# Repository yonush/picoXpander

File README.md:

# Tangible Learning for IoT and Automation ... in a Lunchbox - the picoXpander

This repo is the design files and sample code for the picoXpander kit. It is kit that leverages the Raspberry pico boards (RP2040 & RP2350) as a controller along with various IO boards the connect up using a short ribbon cable. The goal of this kit was to use simple technology to make an interesting electronics kit for teaching at a very affordable price. The focus of the learning is on the programming and understanding logic. This reduces the reliance on the connection and wiring up of individual components which take more time to get right. 

The Lunch box idea idea was create boards that are small enough to fit into a 1L box (about 160L x 113W x 90H mm in size. Like this one from [Living & Co.](https://www.thewarehouse.co.nz/p/living-co-storage-container-rectangle-assorted-1l/R2039528.html)), including the cable. This meant it was easy to keep the kit together and carry around. The 1L box has enough room to fit about 6-7 boards and the USB cable. An example of the lunch with three boards, cable and infomation card can be seen below.

## Software

The kit IO layout was arranged to match the [picoPLC](https://github.com/yonush/PicoPLC) pinout so that you can write your applications using [OpenPLC](https://autonomylogic.com/), CircuitPython, Micropython or C/C++, Python (with Blinka), TinyGo, Nim and Assemnby if you wish. Basically anything that can run on the Raspberyr Pico would work.

Pinout used by the picoXpander and picoPLC

### Using Blinka from Adafruit

Support has been added to work with the Adafruit Blinka platform with some caveats. IN order to match the above pinout and work with the piocPLC there were several changes made to the Adafruit Blinka module. With a summary of the changes below. A more detailed writeup can be found in the [readme](blinka/READ.me) for the picoXpander blinka distribution.

**Changes made to adafruit_blinka module**

The picoXpander driver board uses an off the shelf Raspberry Pico device which means there were no changes made to the USB HID (device VID) settings. We modified the existing rp2040_u2if driver, changes can be found in the blinka folder.

## The boards in brief

There are seven boards identified for the kit with three of them already designed and tested with the other four in progress

- :white_check_mark: Raspberry Pico driver board
- :white_check_mark: Traffic light crossing
- :white_check_mark: 8bit digital I/O
- :white_large_square: Four floor elevator
- :white_large_square: 16x8 LED display
- :white_check_mark: Breakout & passthrough board
- :white_large_square: Multiple sensor board
- :white_large_square: Motor/Servo driver board

### The picoXpander driver board

This board contains a socket for the Pico which also provision for direct soldering of the pico to the board. There is a room for a small I2C OLED display. (supports 0.91", 0.96", 1.3", 1.5" and 2.43" displays). 

- It is 106x88mm in size
- There are 26 buffered LEDs, one for each of the GPIO pins  than connect to the . 
- No external power required.
- Has a convenient reset button
- The I2C can be remapped to "network" two boards using the UART.

### Traffic crossing

This simulates 4 way crossing with a pedestrian light for two of the roads. 

- It is 130x88mm in size
- Three buttons to interact with the lights
- 16 LEDs arrange as 3 per intersection. opposite traffic lights are tied together
- No external power required.

### 8bit Digital IO board

A simple board the maps against the 8 digital inputs and 8 digital outputs. The labels of the buttons are not tied to a specific function but can be used as identifiers.

### Four floor elevator

A board to simulate a elevator with four floors.

- 1 button for each floor to call the elevator 
- 2 LEDs to indicate elevator traveling up or down
- 4 buttons for the inside of the elevator
- 4 LEDs in a box to represent the elevator at each floor
- 1 Analog input for the floor feedback (resistor network)

*Design currently under development.*

### 16x9 LED display

Contains a 16x9 Charlieplexed LED matrix to present a very simple display driven by the rather convenient IS31FL3731 LED display chip.

- 16x9 LEDs (colour yet to be determined)
- 1x 4 way button joystick
- 2x additional buttons for interaction
- 1x Haptic feedback motor

*Design currently under development.*

### Breakout & passthrough board

This board can either be attach to the driver board or between the driver board and another board. It provides the IO passthrough but also a header to allow you to attach dupont leads. A small breadboard is also attached to let you add components not found on the fixed function boards. A 6pin header has been added to provide connectivity for two small servos such as the [MG90S](https://components101.com/motors/mg90s-metal-gear-servo-motor) and the [SG90](https://components101.com/motors/servo-motor-basics-pinout-datasheet).

### Multiple sensor board

This board contains several common sensors and a a couple of RGB LEDs. Starting with the smart sensor BME688. It is an air quality sensor can measure gas, temperature, pressure and humiditthe first gas sensor with Artificial Intelligence  

Sensor list

- Light sensor
- Sound
- Air quality
- Temperature
- Humidity
- Motion
- Pressure

*Design currently under development.*

### Motor/Servo driver board

This board will have a motor driver for two motors to let you attach the pixoXpander to a chassi

- 1x H-bridge motor driver, with built-in short circuit, over current and thermal protection.
- [alt] DRV8833 motor driver using I2C - 1A per motor
- [alt] MX1508 motor driver using PWM - 1.5A per motor
- 2x motors or 1x stepper
- Uses external power with on board charger for a battery
- 4x servo outputs
- power switch for the external power

*Design currently under development.*

## Demo code

*Under development*

-end-of-file-

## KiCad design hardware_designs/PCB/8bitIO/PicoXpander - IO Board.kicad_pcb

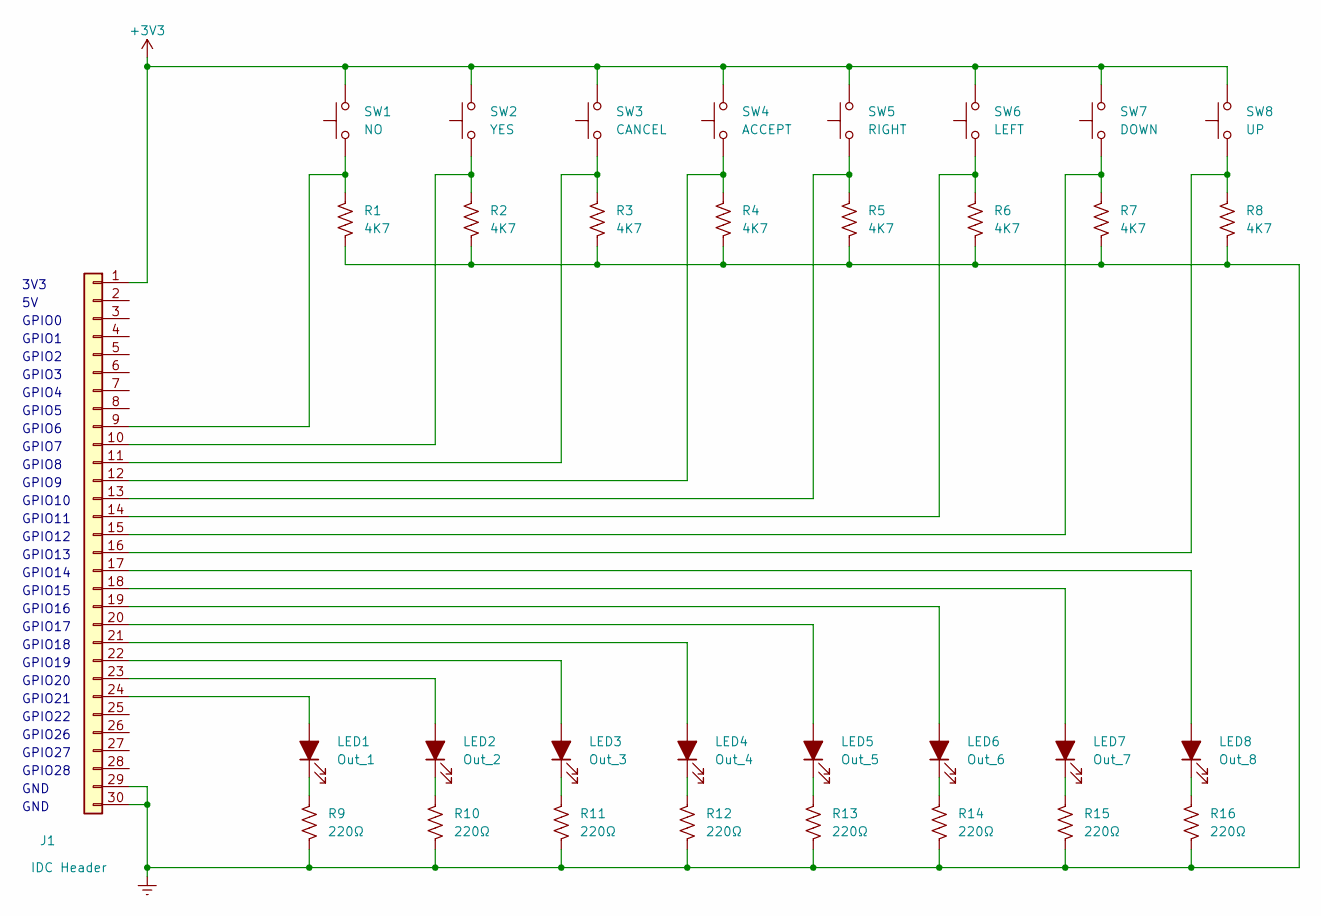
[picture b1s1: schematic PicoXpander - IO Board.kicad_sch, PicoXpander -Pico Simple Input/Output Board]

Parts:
J1: IDC Header; IDC-Header_2x15_P2.54mm_Horizontal
LED1, LED2, LED3, LED4, LED5, LED6, LED7, LED8: Red; LED_0805_2012Metric
R1, R2, R3, R4, R5, R6, R7, R8: 4K7; R_0805_2012Metric
R9, R10, R11, R12, R13, R14, R15, R16: 220Ω; R_0805_2012Metric
SW1: NO; SW_Push_1P1T_NO_6x6mm_H9.5mm
SW2: YES; SW_Push_1P1T_NO_6x6mm_H9.5mm
SW3: CANCEL; SW_Push_1P1T_NO_6x6mm_H9.5mm
SW4: ACCEPT; SW_Push_1P1T_NO_6x6mm_H9.5mm
SW5: RIGHT; SW_Push_1P1T_NO_6x6mm_H9.5mm
SW6: LEFT; SW_Push_1P1T_NO_6x6mm_H9.5mm
SW7: DOWN; SW_Push_1P1T_NO_6x6mm_H9.5mm
SW8: UP; SW_Push_1P1T_NO_6x6mm_H9.5mm

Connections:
+3V3: J1.1, SW1.2, SW2.2, SW3.2, SW4.2, SW5.2, SW6.2, SW7.2, SW8.2
GNDREF: J1.29, J1.30, R1.1, R2.1, R3.1, R4.1, R5.1, R6.1, R7.1, R8.1, R9.1, R10.1, R11.1, R12.1, R13.1, R14.1, R15.1, R16.1
unnamed: J1.9, R1.2, SW1.1
unnamed: J1.10, R2.2, SW2.1
unnamed: J1.11, R3.2, SW3.1
unnamed: J1.12, R4.2, SW4.1
unnamed: J1.13, R5.2, SW5.1
unnamed: J1.14, R6.2, SW6.1
unnamed: J1.15, R7.2, SW7.1
unnamed: J1.16, R8.2, SW8.1
unnamed: J1.17, LED8.2 (A)
unnamed: J1.18, LED7.2 (A)
unnamed: J1.19, LED6.2 (A)
unnamed: J1.20, LED5.2 (A)
unnamed: J1.21, LED4.2 (A)
unnamed: J1.22, LED3.2 (A)
unnamed: J1.23, LED2.2 (A)
unnamed: J1.24, LED1.2 (A)
unnamed: LED1.1 (K), R9.2
unnamed: LED2.1 (K), R10.2
unnamed: LED3.1 (K), R11.2
unnamed: LED4.1 (K), R12.2
unnamed: LED5.1 (K), R13.2
unnamed: LED6.1 (K), R14.2
unnamed: LED7.1 (K), R15.2
unnamed: LED8.1 (K), R16.2

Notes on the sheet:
GPIO13
GPIO19
GPIO0
GPIO3
GPIO17
GPIO20
GPIO21
GPIO2
3V3
GPIO15
GPIO14
GPIO8
GPIO12
GPIO16
GPIO6
GPIO7
GPIO27
GND
GPIO18
GPIO10
GPIO22
GPIO9
GPIO11
GPIO1
GPIO4
GPIO28
GPIO26
GPIO5

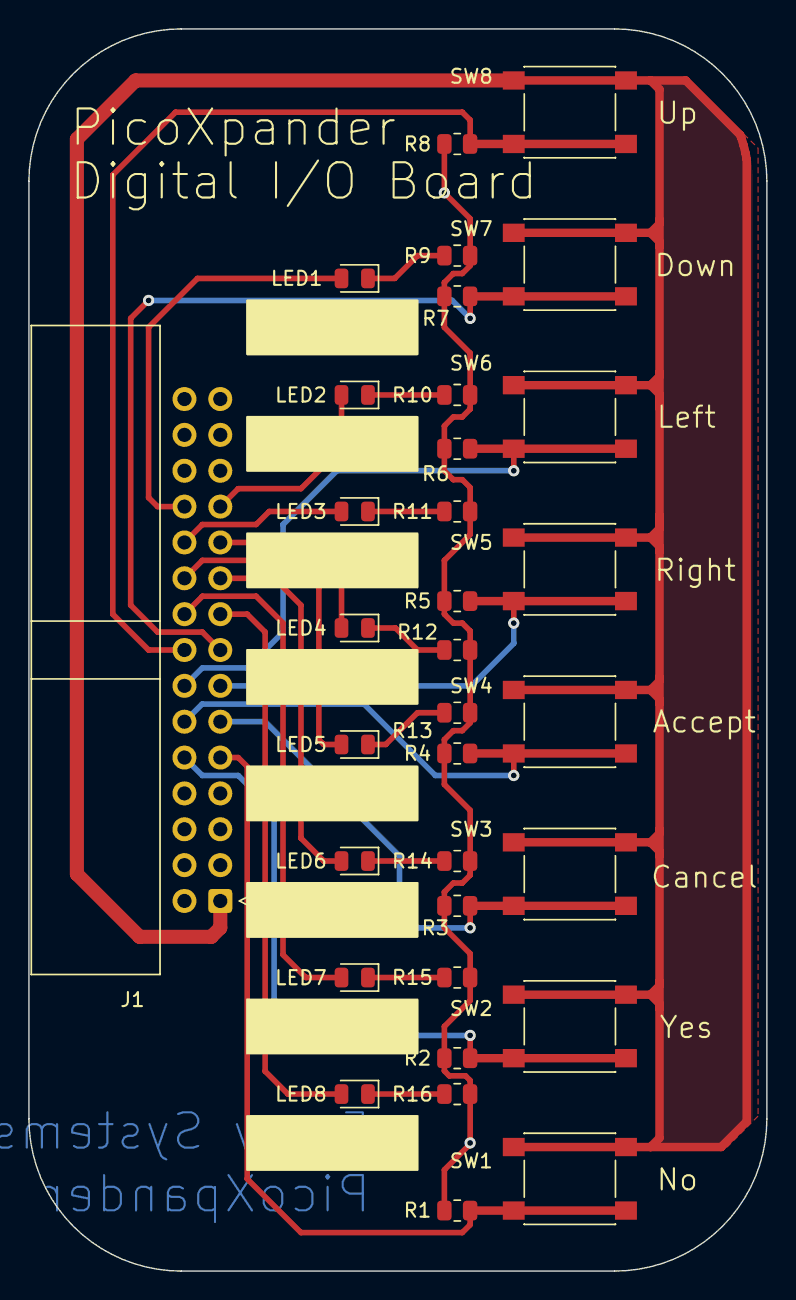
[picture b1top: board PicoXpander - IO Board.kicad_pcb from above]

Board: 2 copper layers, 52.3 x 88.0 mm, 33 parts (0 on the bottom side), 26 nets.

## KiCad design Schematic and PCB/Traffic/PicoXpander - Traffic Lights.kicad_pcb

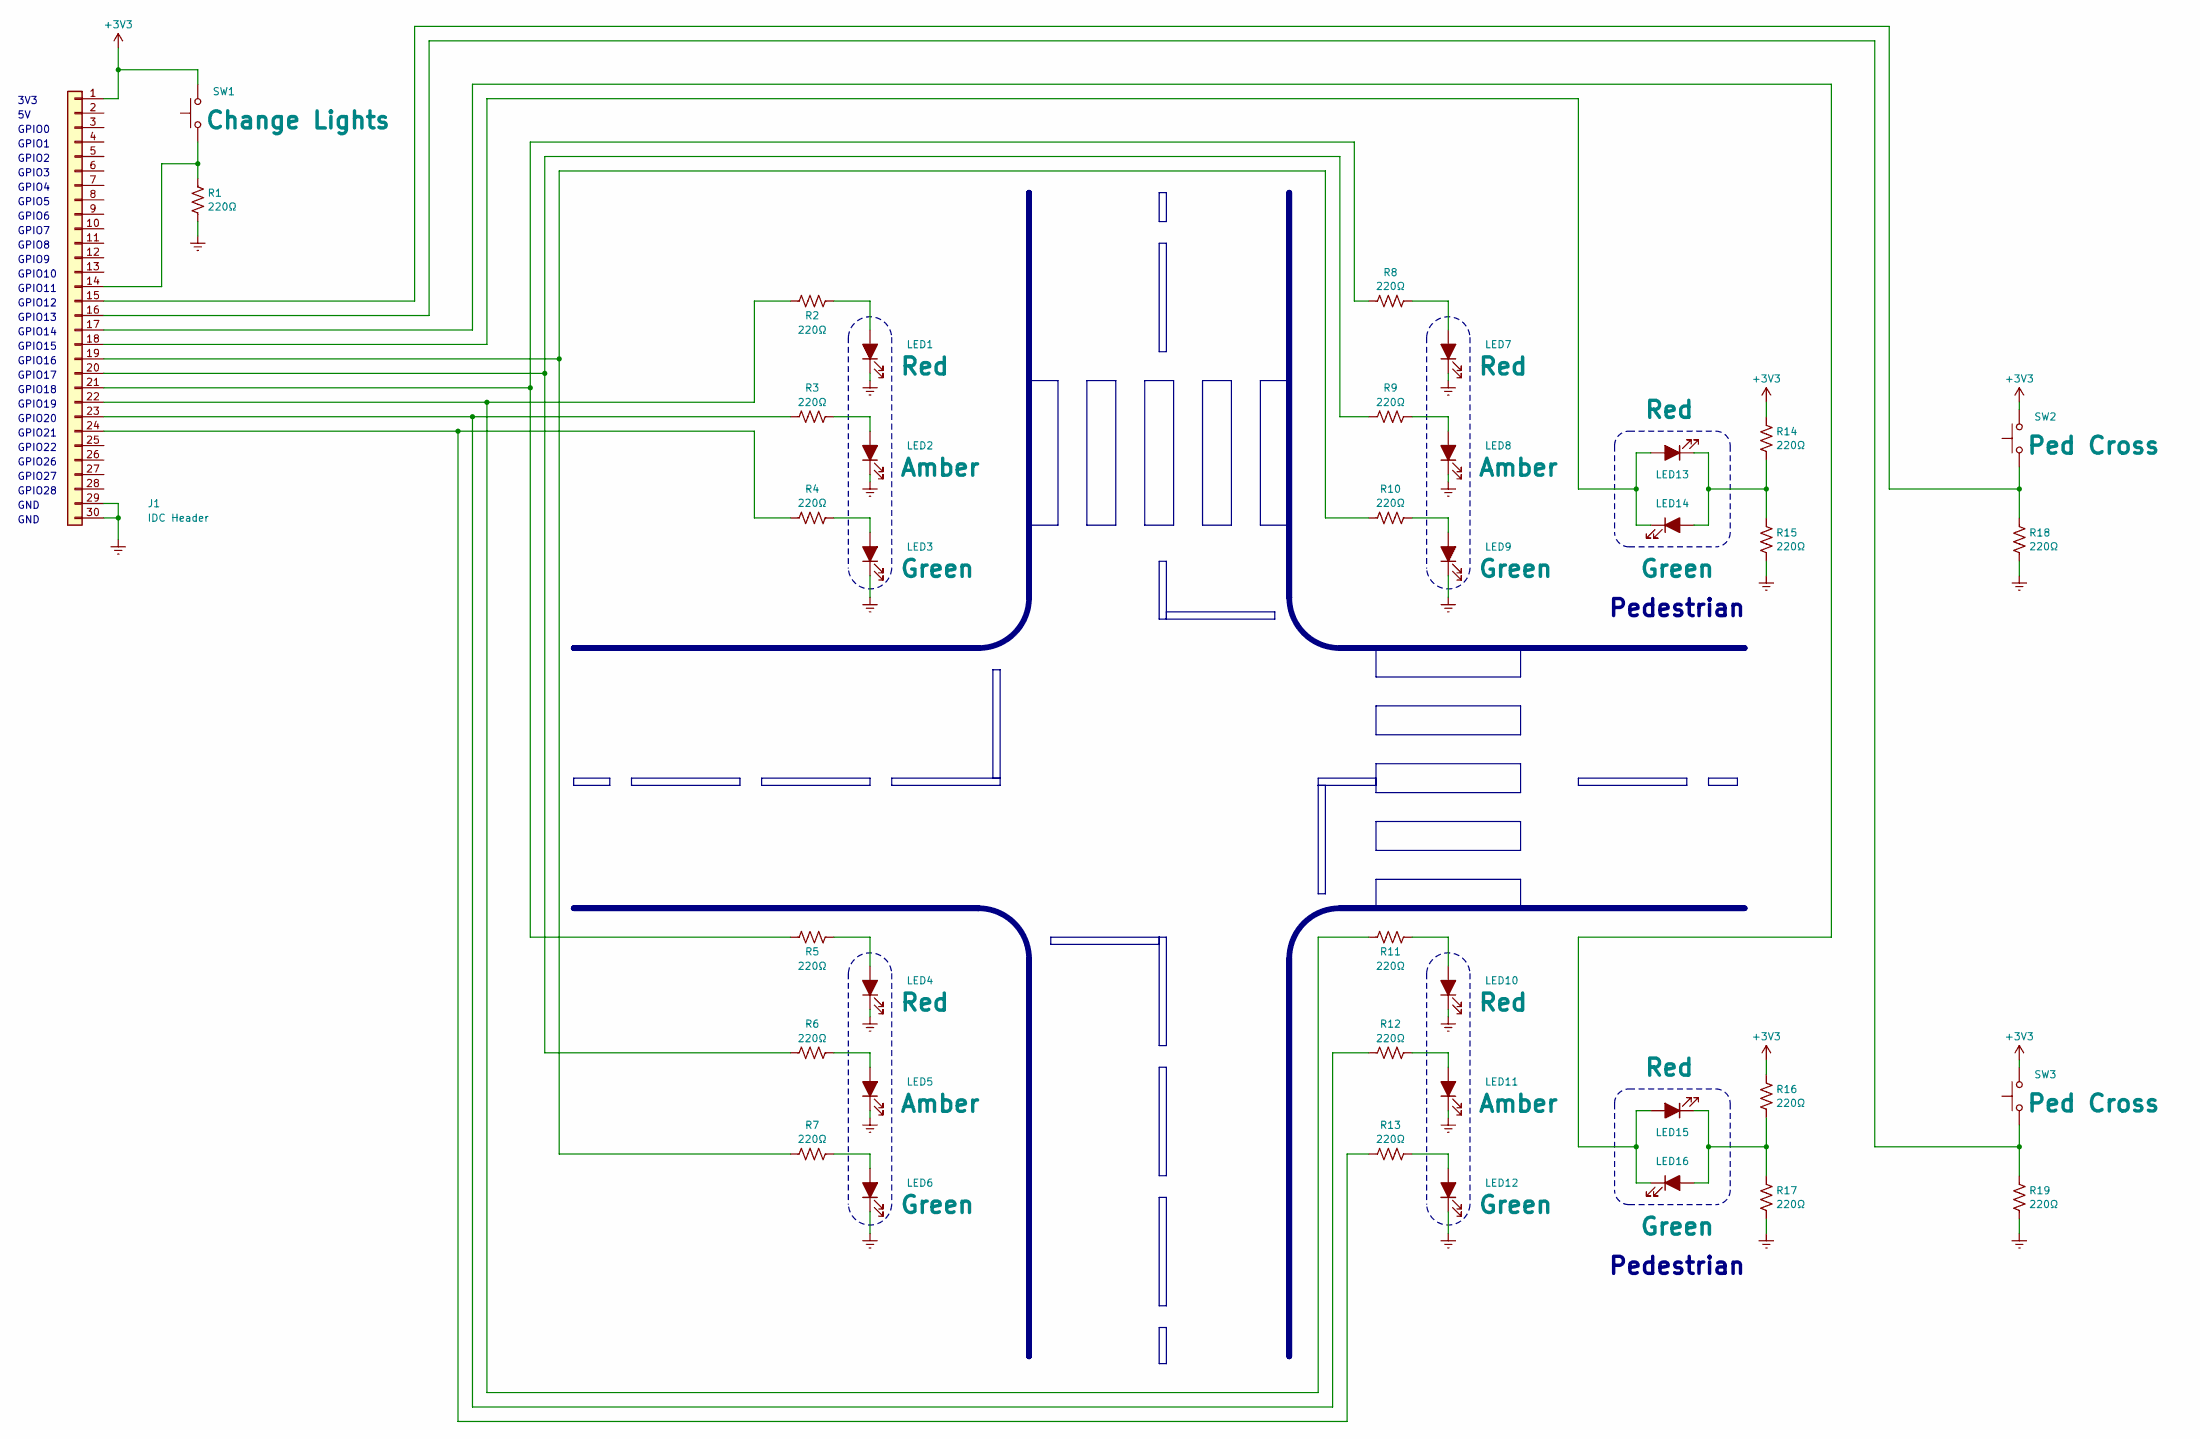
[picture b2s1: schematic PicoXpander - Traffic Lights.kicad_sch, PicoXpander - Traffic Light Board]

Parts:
J1: IDC Header; IDC-Header_2x15_P2.54mm_Horizontal
LED1, LED4, LED7, LED10, LED13, LED15: Red; LED_0805_2012Metric
LED2, LED5, LED8, LED11: Amber; LED_0805_2012Metric
LED3, LED6, LED9, LED12, LED14, LED16: Green; LED_0805_2012Metric
R1, R2, R3, R4, R5, R6, R7, R8, R9, R10, R11, R12, R13, R14, R15, R16, R17, R18, R19: 220Ω; R_0805_2012Metric
SW1: Change Lights; SW_Push_1P1T_NO_6x6mm_H9.5mm
SW2, SW3: Ped Cross; SW_Push_1P1T_NO_6x6mm_H9.5mm

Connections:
+3V3: J1.1, R14.2, R16.2, SW1.2, SW2.2, SW3.2
GNDREF: J1.29, J1.30, LED1.1 (K), LED2.1 (K), LED3.1 (K), LED4.1 (K), LED5.1 (K), LED6.1 (K), LED7.1 (K), LED8.1 (K), LED9.1 (K), LED10.1 (K), LED11.1 (K), LED12.1 (K), R1.1, R15.1, R17.1, R18.1, R19.1
unnamed: J1.14, R1.2, SW1.1
unnamed: J1.15, R18.2, SW2.1
unnamed: J1.16, R19.2, SW3.1
unnamed: J1.17, LED15.2 (A), LED16.1 (K)
unnamed: J1.18, LED13.2 (A), LED14.1 (K)
unnamed: J1.19, R7.1, R10.1
unnamed: J1.20, R6.1, R9.1
unnamed: J1.21, R5.1, R8.1
unnamed: J1.22, R2.1, R11.1
unnamed: J1.23, R3.1, R12.1
unnamed: J1.24, R4.1, R13.1
unnamed: LED1.2 (A), R2.2
unnamed: LED2.2 (A), R3.2
unnamed: LED3.2 (A), R4.2
unnamed: LED4.2 (A), R5.2
unnamed: LED5.2 (A), R6.2
unnamed: LED6.2 (A), R7.2
unnamed: LED7.2 (A), R8.2
unnamed: LED8.2 (A), R9.2
unnamed: LED9.2 (A), R10.2
unnamed: LED10.2 (A), R11.2
unnamed: LED11.2 (A), R12.2
unnamed: LED12.2 (A), R13.2
unnamed: LED13.1 (K), LED14.2 (A), R14.1, R15.2
unnamed: LED15.1 (K), LED16.2 (A), R16.1, R17.2

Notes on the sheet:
GPIO13
GPIO19
GPIO0
GPIO3
GPIO17
GPIO20
GPIO21
GPIO2
3V3
GPIO15
GPIO14
Pedestrian
GPIO8
GPIO12
GPIO16
GPIO6
GPIO7
GPIO27
GND
GPIO18
GPIO10
GPIO22
GPIO9
GPIO11
GPIO1
GPIO4
GPIO28
GPIO26
GPIO5

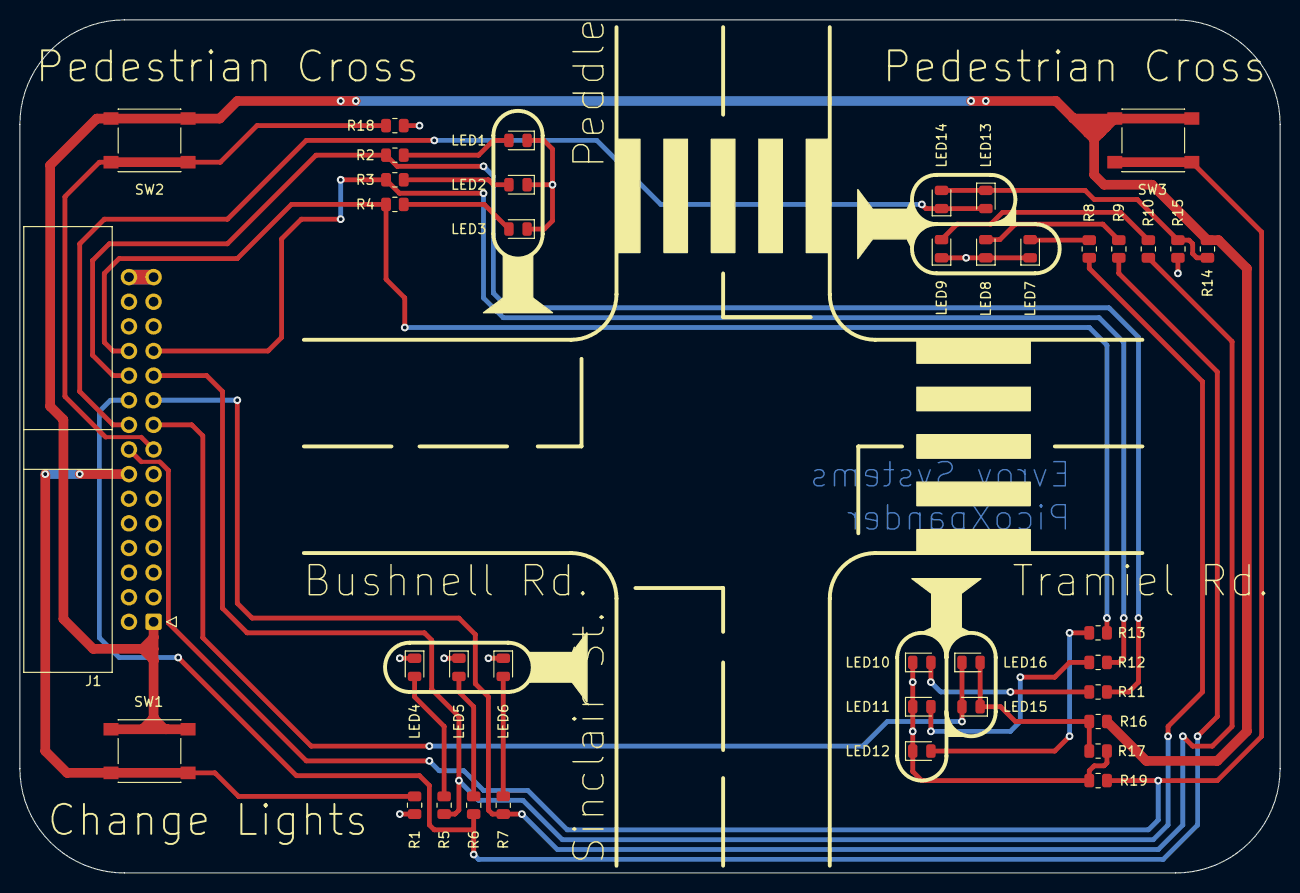
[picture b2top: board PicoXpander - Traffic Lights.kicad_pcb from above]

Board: 2 copper layers, 130.0 x 88.0 mm, 39 parts (0 on the bottom side), 27 nets.

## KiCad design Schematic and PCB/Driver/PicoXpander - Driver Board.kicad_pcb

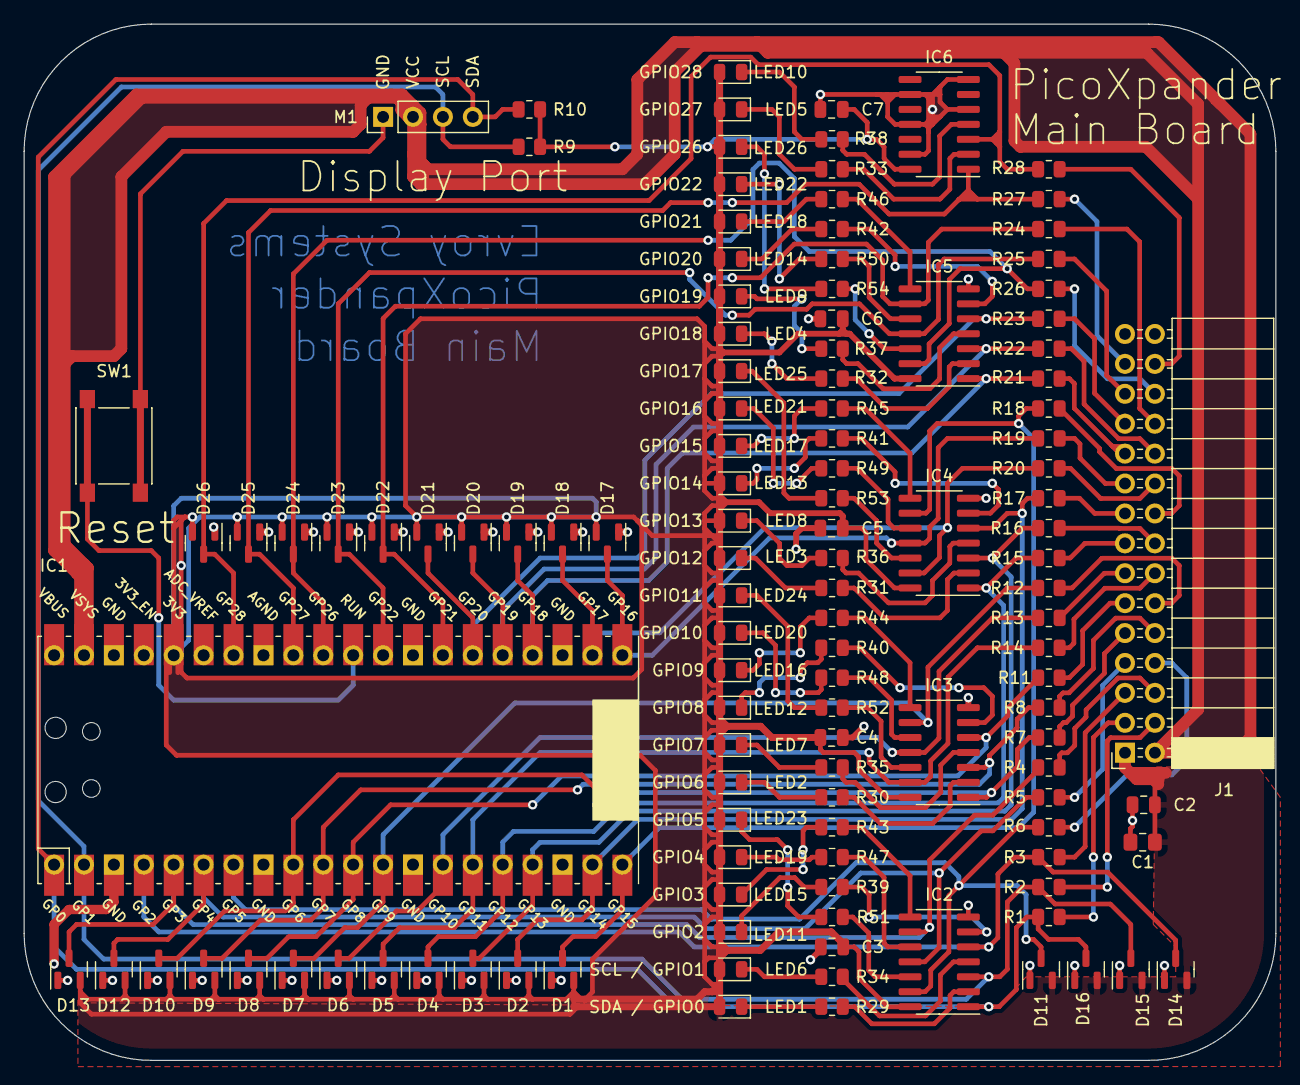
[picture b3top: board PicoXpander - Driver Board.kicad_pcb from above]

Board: 2 copper layers, 106.3 x 88.0 mm, 122 parts (0 on the bottom side), 108 nets.

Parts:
C1: 10µF; C_0805_2012Metric_Pad1.18x1.45mm_HandSolder
C2, C3, C4, C5, C6, C7: 100n; C_0805_2012Metric
D1, D2, D3, D4, D5, D6, D7, D8, D9, D10, D11, D12, D13, D14, D15, D16, D17, D18, D19, D20, D21, D22, D23, D24, D25, D26: BAT721S; SOT-23
IC1: Pico; RPi_Pico_SMD_TH
IC2, IC3, IC4, IC5, IC6: 74LVC06; SOIC-14_3.9x8.7mm_P1.27mm
J1: IDC Header; PinSocket_2x15_P2.54mm_Horizontal
LED1, LED2, LED3, LED4, LED5, LED6, LED7, LED8, LED9, LED10, LED11, LED12, LED13, LED14, LED15, LED16, LED17, LED18, LED19, LED20, LED21, LED22, LED23, LED24, LED25, LED26: Red; LED_0805_2012Metric
M1: Display Module OLED I2C; PinHeader_1x04_P2.54mm_Vertical
R1, R2, R3, R4, R5, R6, R7, R8, R11, R12, R13, R14, R15, R16, R17, R18, R19, R20, R21, R22, R23, R24, R25, R26, R27, R28: 22Ω; R_0805_2012Metric
R9, R10: 4K7; R_0805_2012Metric
R29, R30, R31, R32, R33, R34, R35, R36, R37, R38, R39, R40, R41, R42, R43, R44, R45, R46, R47, R48, R49, R50, R51, R52, R53, R54: 220Ω; R_0805_2012Metric
SW1: Reset; SW_Push_1P1T_NO_6x6mm_H9.5mm

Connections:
+3V3: C1.1, C2.1, C3.1, C4.1, C5.1, C6.1, C7.1, D1.2 (K), D2.2 (K), D3.2 (K), D4.2 (K), D5.2 (K), D6.2 (K), D7.2 (K), D8.2 (K), D9.2 (K), D10.2 (K), D11.2 (K), D12.2 (K), D13.2 (K), D14.2 (K), D15.2 (K), D16.2 (K), D17.2 (K), D18.2 (K), D19.2 (K), D20.2 (K), D21.2 (K), D22.2 (K), D23.2 (K), D24.2 (K), D25.2 (K), D26.2 (K), IC1.36 (3V3), IC2.14 (VCC), IC3.14 (VCC), IC4.14 (VCC), IC5.14 (VCC), IC6.14 (VCC), J1.1, LED1.2 (A), LED2.2 (A), LED3.2 (A), LED4.2 (A), LED5.2 (A), LED6.2 (A), LED7.2 (A), LED8.2 (A), LED9.2 (A), LED10.2 (A), LED11.2 (A), LED12.2 (A), LED13.2 (A), LED14.2 (A), LED15.2 (A), LED16.2 (A), LED17.2 (A), LED18.2 (A), LED19.2 (A), LED20.2 (A), LED21.2 (A), LED22.2 (A), LED23.2 (A), LED24.2 (A), LED25.2 (A), LED26.2 (A), R9.2, R10.2
+5V: IC1.39 (VSYS), J1.2, M1.2 (VCC)
/GPIO Status LED's/GPIO0: D16.3 (A), IC1.1 (GPIO0), IC2.1, M1.4 (SDA), R1.1, R10.1
/GPIO Status LED's/GPIO1: D15.3 (A), IC1.2 (GPIO1), IC2.3, M1.3 (SCL), R2.1, R9.1
/GPIO Status LED's/GPIO2: D14.3 (A), IC1.4 (GPIO2), IC2.5, R3.1
/GPIO Status LED's/GPIO3: D13.3 (A), IC1.5 (GPIO3), IC2.9, R4.1
/GPIO Status LED's/GPIO4: D12.3 (A), IC1.6 (GPIO4), IC2.11, R5.1
/GPIO Status LED's/GPIO5: D11.3 (A), IC1.7 (GPIO5), IC2.13, R6.1
/GPIO Status LED's/GPIO6: D10.3 (A), IC1.9 (GPIO6), IC3.1, R7.1
/GPIO Status LED's/GPIO7: D9.3 (A), IC1.10 (GPIO7), IC3.3, R8.1
/GPIO Status LED's/GPIO8: D8.3 (A), IC1.11 (GPIO8), IC3.5, R11.1
/GPIO Status LED's/GPIO9: D7.3 (A), IC1.12 (GPIO9), IC3.9, R12.1
/GPIO Status LED's/GPIO10: D6.3 (A), IC1.14 (GPIO10), IC3.11, R13.1
/GPIO Status LED's/GPIO11: D5.3 (A), IC1.15 (GPIO11), IC3.13, R14.1
/GPIO Status LED's/GPIO12: D4.3 (A), IC1.16 (GPIO12), IC4.1, R15.1
/GPIO Status LED's/GPIO13: D3.3 (A), IC1.17 (GPIO13), IC4.3, R16.1
/GPIO Status LED's/GPIO14: D2.3 (A), IC1.19 (GPIO14), IC4.5, R17.1
/GPIO Status LED's/GPIO15: D1.3 (A), IC1.20 (GPIO15), IC4.9, R18.1
/GPIO Status LED's/GPIO16: D17.3 (A), IC1.21 (GPIO16), IC4.11, R19.1
/GPIO Status LED's/GPIO17: D18.3 (A), IC1.22 (GPIO17), IC4.13, R20.1
/GPIO Status LED's/GPIO18: D19.3 (A), IC1.24 (GPIO18), IC5.1, R21.1
/GPIO Status LED's/GPIO19: D20.3 (A), IC1.25 (GPIO19), IC5.3, R22.1
/GPIO Status LED's/GPIO20: D21.3 (A), IC1.26 (GPIO20), IC5.5, R23.1
/GPIO Status LED's/GPIO21: D22.3 (A), IC1.27 (GPIO21), IC5.9, R24.1
/GPIO Status LED's/GPIO22: D23.3 (A), IC1.29 (GPIO22), IC5.11, R25.1
/GPIO Status LED's/GPIO26: D24.3 (A), IC1.31 (GPIO26_ADC0), IC5.13, R26.1
/GPIO Status LED's/GPIO27: D25.3 (A), IC1.32 (GPIO27_ADC1), IC6.1, R27.1
/GPIO Status LED's/GPIO28: D26.3 (A), IC1.34 (GPIO28_ADC2), IC6.3, R28.1
GNDREF: C1.2, C2.2, C3.2, C4.2, C5.2, C6.2, C7.2, D1.1 (K), D2.1 (K), D3.1 (K), D4.1 (K), D5.1 (K), D6.1 (K), D7.1 (K), D8.1 (K), D9.1 (K), D10.1 (K), D11.1 (K), D12.1 (K), D13.1 (K), D14.1 (K), D15.1 (K), D16.1 (K), D17.1 (K), D18.1 (K), D19.1 (K), D20.1 (K), D21.1 (K), D22.1 (K), D23.1 (K), D24.1 (K), D25.1 (K), D26.1 (K), IC1.3 (GND), IC1.8 (GND), IC1.13 (GND), IC1.18 (GND), IC1.23 (GND), IC1.28 (GND), IC1.33 (AGND), IC1.38 (GND), IC2.7 (GND), IC3.7 (GND), IC4.7 (GND), IC5.7 (GND), IC6.5, IC6.7 (GND), IC6.9, IC6.11, IC6.13, J1.29, J1.30, M1.1 (GND), SW1.1
unnamed: IC1.30 (RUN), SW1.2
unnamed: IC2.2, R29.1
unnamed: IC2.4, R34.1
unnamed: IC2.6, R39.1
unnamed: IC2.8, R43.1
unnamed: IC2.10, R47.1
unnamed: IC2.12, R51.1
unnamed: IC3.2, R30.1
unnamed: IC3.4, R35.1
unnamed: IC3.6, R40.1
unnamed: IC3.8, R44.1
unnamed: IC3.10, R48.1
unnamed: IC3.12, R52.1
unnamed: IC4.2, R31.1
unnamed: IC4.4, R36.1
unnamed: IC4.6, R41.1
unnamed: IC4.8, R45.1
unnamed: IC4.10, R49.1
unnamed: IC4.12, R53.1
unnamed: IC5.2, R32.1
unnamed: IC5.4, R37.1
unnamed: IC5.6, R42.1
unnamed: IC5.8, R46.1
unnamed: IC5.10, R50.1
unnamed: IC5.12, R54.1
unnamed: IC6.2, R33.1
unnamed: IC6.4, R38.1
unnamed: J1.3, R1.2
unnamed: J1.4, R2.2
unnamed: J1.5, R3.2
unnamed: J1.6, R4.2
unnamed: J1.7, R5.2
unnamed: J1.8, R6.2
unnamed: J1.9, R7.2
unnamed: J1.10, R8.2
unnamed: J1.11, R11.2
unnamed: J1.12, R12.2
unnamed: J1.13, R13.2
unnamed: J1.14, R14.2
unnamed: J1.15, R15.2
unnamed: J1.16, R16.2
unnamed: J1.17, R17.2
unnamed: J1.18, R18.2
unnamed: J1.19, R19.2
unnamed: J1.20, R20.2
unnamed: J1.21, R21.2
unnamed: J1.22, R22.2
unnamed: J1.23, R23.2
unnamed: J1.24, R24.2
unnamed: J1.25, R25.2
unnamed: J1.26, R26.2
unnamed: J1.27, R27.2
unnamed: J1.28, R28.2
unnamed: LED1.1 (K), R29.2
unnamed: LED2.1 (K), R30.2
unnamed: LED3.1 (K), R31.2
unnamed: LED4.1 (K), R32.2
unnamed: LED5.1 (K), R33.2
unnamed: LED6.1 (K), R34.2
unnamed: LED7.1 (K), R35.2
unnamed: LED8.1 (K), R36.2
unnamed: LED9.1 (K), R37.2
unnamed: LED10.1 (K), R38.2
unnamed: LED11.1 (K), R39.2
unnamed: LED12.1 (K), R40.2
unnamed: LED13.1 (K), R41.2
unnamed: LED14.1 (K), R42.2
unnamed: LED15.1 (K), R43.2
unnamed: LED16.1 (K), R44.2
unnamed: LED17.1 (K), R45.2
unnamed: LED18.1 (K), R46.2
unnamed: LED19.1 (K), R47.2
unnamed: LED20.1 (K), R48.2
unnamed: LED21.1 (K), R49.2
unnamed: LED22.1 (K), R50.2
unnamed: LED23.1 (K), R51.2
unnamed: LED24.1 (K), R52.2
unnamed: LED25.1 (K), R53.2
unnamed: LED26.1 (K), R54.2

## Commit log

2024-11-15 initial repo
2024-11-15 fixed typos...
2024-11-19 Rearranged folders, added Blinka platform
2024-11-19 Minor edit
2024-11-22 Add guizero demo and update xpander OLED functions
2024-11-22 Update README.md
    Added photos for the three boards
2024-11-22 Added TinyGO board files for the picoXpander
2024-11-23 Added PWM & ADC samples
2024-11-23 Added the breakout board design
2024-11-23 Minor edits
2024-11-23 Updated Blinka notes
2024-11-23 Updated U2IF notes
2024-11-23 updates to demo code
2024-11-24 Added shematic for the breakout board
2024-11-24 new image for breakoput board
2024-11-25 Various updates and fixes
2024-11-25 Added MAX7219 demo, fixed bugs
2024-11-26 Minor updates
2024-11-29 Updated FW to support picow/pico2/pico2w
2024-12-07 Added range checking to Xpander
2025-02-13 Updated many demos and core library
2025-02-16 Add files via upload
    Image of the lunch box used
2025-02-16 Update README.md
    Added the lunchbox iamge
2025-02-16 updated lunch image
2025-02-16 updated lunchbox image to png
2025-02-16 Update README.md
    Fixed image url
2025-02-18 Update elevator spec for 4 floors
2025-02-23 added BoMs, updated sensor schematic
